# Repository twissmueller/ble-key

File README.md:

# ble-key

A Bluetooth Low Energy interface for a Morse **key**, built on a Seeed Studio XIAO board —
either the [XIAO ESP32-S3](https://wiki.seeedstudio.com/xiao_esp32s3_getting_started/) or the
[XIAO nRF52840](https://wiki.seeedstudio.com/XIAO_BLE/).

Plug in your own straight key or iambic paddle. The board reads the contacts (dit / dah),
debounces them, and streams **timed keying edges** over BLE as notifications to the
[Longpath](https://wissmueller.net/en/longpath.html) Morse-training app, which produces the
audio/sidetone and does the training. The device itself makes no sound — it's purely the
key interface. The onboard LED gives instant, BLE-independent visual feedback while keying.

The BLE contract below is simple and app-agnostic — anything that speaks GATT can consume it.
Both boards implement it identically; the app cannot tell them apart.

## Setting up your key

Plug your key or paddle (for example a Xiegu VK-5) into the 3.5 mm jack: tip is dit, ring is
dah, sleeve is ground; a straight key uses tip and sleeve only. Power the key from USB-C, then
connect to it from the Longpath app — it shows up as `Paddle`. The LED lights while you key,
so you can check the paddle before Bluetooth is involved. If dit and dah come out swapped,
switch your paddle's reverse setting (or its cable), not the key. A battery key sleeps after
ten idle minutes off USB; the first press only wakes it.

## Repository layout

| Path | What |
|------|------|
| [`esp32s3/`](esp32s3/) | XIAO ESP32-S3: firmware, pins and wiring, the battery mod ([BATTERY.md](esp32s3/BATTERY.md)) |
| [`nrf52840/`](nrf52840/) | XIAO nRF52840: firmware, pins and wiring, battery |
| [`lib/BleKeyCore/`](lib/BleKeyCore/src/BleKeyCore.h) | Shared firmware: the BLE contract, debounce, LiPo curve, power states |
| [`enclosure/`](enclosure/) | Printable cases — the XIAO case fits both boards |
| `flash.sh`, `monitor.sh` | Build, flash and watch either board |

## Which board?

| | XIAO ESP32-S3 | XIAO nRF52840 |
|---|---|---|
| Keying, LED, BLE contract | ✓ | ✓ |
| Wiring of the paddle jack | `D1` tip, `D2` ring, `GND` sleeve | the same |
| Battery level | LiPo **plus two dividers** soldered on | LiPo only — divider is on the board |
| Charging / charged | extra charge-sense wire | read from the charger on the board |
| Idle sleep | deep sleep, ~14 µA | System OFF, a few µA |
| Current while connected | tens of mA | a few mA (typical figures, not measured here) |

For a battery key the nRF52840 is the better choice: no extra parts and much longer runtime.
The ESP32-S3 key stays supported.

## Getting a key

The BLE key is open hardware — get one in whichever way suits you:

1. **Buy a ready-built key** in the [Ramus Labs Shop](https://shop.ramuslabs.com/ble-key/):
   assembled, flashed, and tested, in three cases (Mini, Compact, Modular).
2. **Build it yourself** — source the parts ([Hardware](#hardware)) and flash the firmware
   ([Build & flash](#build--flash)); everything you need is in this repository.

The Longpath app's BLE-key dialog offers only the shop (its address is set in Longpath's Darwin
config, `ble_key_shop_url`); building it yourself is documented here.

## BLE contract

The device advertises as **`Paddle`** with one service and one notify characteristic.
On every debounced paddle edge it sends a **5-byte little-endian** packet:

```
byte 0     : event   (uint8)
bytes 1..4 : millis  (uint32, little-endian) — device millis() at the edge
```

Events:

| Value | Event      |
|-------|------------|
| `0`   | `DIT_DOWN` |
| `1`   | `DIT_UP`   |
| `2`   | `DAH_DOWN` |
| `3`   | `DAH_UP`   |

The client reconstructs element and gap timing from consecutive timestamps. The board
re-advertises automatically after a central disconnects, so a client can reconnect
without power-cycling.

### Battery level

With a battery the key additionally exposes the SIG-standard
**Battery Service `0x180F`** with the **Battery Level characteristic `0x2A19`** (`uint8`,
0–100 %, read + notify). The level is re-measured every 10 s while the key is idle and
notified only when it changes; a client reads it once after connecting and then subscribes.
The service is *not* advertised — clients find it during service discovery — and it sits
next to the Longpath service without touching the packet format or UUIDs above. Clients
that do not know it, and older app builds, simply ignore it. Whether a key without a cell
exposes the service at all depends on the board (see its README); either way the Longpath
app then shows no level.

The percentage comes from an open-circuit LiPo discharge curve (3.30 V → 0 %, 4.20 V →
100 %, flat in the middle), not a linear map. On USB power the
measurement would only see the charger, so the key publishes **`0xFF` = level unknown** instead
of a percentage — outside the SIG's 0–100 on purpose; Longpath shows no level for it, other
clients should treat it the same way — and the idle sleep is off. Below 3.5 V the onboard
LED double-blinks once at boot, independently of BLE.

### Battery power state

Next to the level the same service carries the SIG-standard **Battery Power State
characteristic `0x2A1A`** (`uint8`, read + notify): bits 0–1 *present*, bits 2–3
*discharging*, bits 4–5 *charging* (each 2 = no, 3 = yes; 0 = unknown), bits 6–7 unused.
The key publishes five values:

| Meaning   | Value  | present | discharging | charging |
|-----------|--------|---------|-------------|----------|
| unknown   | `0x00` | ?       | ?           | ?        |
| on cell   | `0x2F` | yes     | yes         | no       |
| charging  | `0x3B` | yes     | no          | yes      |
| charged   | `0x2B` | yes     | no          | no       |
| no cell   | `0x02` | no      | —           | —        |

Off USB a plausible cell reading means *on cell*. On USB the charger's status line is the
only evidence; how each board reads it is in its README. Anything the key cannot vouch for
stays *unknown*. While *charging* or *charged* the level in `0x2A19`
is the live reading of the cell under charge instead of `0xFF` — a few points high and
climbing; the Longpath app shows it next to "charging" and forces 100 % once the key reports
*charged*. In every other state on USB the level stays `0xFF`. Notified only on change; a
client reads it once after connecting and subscribes.

### Idle sleep

A battery key enters deep sleep after ten minutes without a paddle edge.
It disconnects the central first, so a client sees a clean disconnect rather than a
supervision timeout, and wakes on either paddle line going LOW. Waking is a reset: the key
advertises again after about half a second, and `millis()` restarts at 0 — clients must
treat a reconnect as a timing resync (Longpath does). A key on USB never sleeps.

### UUIDs

The service and characteristic UUIDs in [`BleKeyCore.h`](lib/BleKeyCore/src/BleKeyCore.h) are the **fixed Longpath contract**
— the app looks for exactly this service, so leave them unchanged if your key should work
with Longpath (whether self-built, from a kit, or bought ready-made). Only when building
for a *different* client should you mint your own pair (`uuidgen`, run twice) and replace
`SVC_UUID` / `CHR_UUID` there — both boards pick them up.

## Build & flash

Requires [`arduino-cli`](https://arduino.github.io/arduino-cli/) and the core for your board:

```sh
# XIAO ESP32-S3
arduino-cli core install esp32:esp32
arduino-cli lib install "NimBLE-Arduino"

# XIAO nRF52840 (Seeed's non-mbed core, which brings the Bluefruit BLE library)
arduino-cli config add board_manager.additional_urls \
  https://files.seeedstudio.com/arduino/package_seeeduino_boards_index.json
arduino-cli core update-index
arduino-cli core install Seeeduino:nrf52
```

Then:

```sh
./flash.sh esp32s3            # or: ./flash.sh nrf52840
./flash.sh nrf52840 /dev/cu.usbmodemXXXX   # pass the port explicitly

./monitor.sh                  # serial monitor at 115200 baud, either board
```

`flash.sh` passes the shared `lib/BleKeyCore` to arduino-cli with `--library`; a manual
`arduino-cli compile` needs the same flag. Bench builds and board-specific notes are in
[esp32s3/README.md](esp32s3/README.md) and [nrf52840/README.md](nrf52840/README.md).

## License

[MIT](LICENSE) © 2026 Tobias Wissmüller

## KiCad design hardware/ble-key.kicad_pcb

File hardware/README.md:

# ble-key nRF52840 board — schematic

The custom board from [PCB-PLAN.md](../PCB-PLAN.md): a Raytac MDBT50Q-1MV2 (nRF52840), a BQ24074
charger with power path, USB-C, a 3.5 mm paddle jack and a JST-PH socket for the LiPo.

| File | What |
|---|---|
| `ble-key.kicad_pro`, `ble-key.kicad_sch` | KiCad 10 project and schematic — open the project in KiCad |
| `ble-key-schematic.pdf` | the schematic as a PDF |
| `ble-key-bom.csv` | parts list with MPNs where chosen |
| `gen_schematic.py` | generates the schematic; the parts, values and nets live here |
| `ble-key.kicad_pcb` | the board: 48 × 27 mm, 2 layers, routed |
| `gen_board.py` | places the footprints, draws outline, holes, pours and the antenna keep-out |
| `route.py` | autoroutes the board with Freerouting, stitches the ground pours and refills them |
| `board-top.png`, `board-bottom.png` | renders of the routed board |
| `export_jlc.py`, `jlcpcb/` | JLCPCB production files: Gerbers + drill (zip), BOM and placement (CPL) |

**Status:** schematic and a first routed layout. ERC: 0 errors. DRC: 0 errors and 0 unconnected
pads; the remaining warnings are the paddle jack's outline crossing the board edge (its opening
overhangs the edge on purpose) and, until KiCad has been opened once, "library not in the
configuration" notices.

## Design

| Block | Choice |
|---|---|
| USB-C | GCT USB4105, 5.1 kΩ on CC1/CC2 (5 V sink), USBLC6-2SC6 ESD, 27 Ω series resistors to the module (Raytac reference) |
| Charger | BQ24074: 175 mA charge (R_ISET 5.1 kΩ, 0.5 C for 350 mAh), 500 mA input limit (R_ILIM 3.09 kΩ, EN2 = 1, EN1 = 0), TS on 10 kΩ (no thermistor), ITERM and TMR open for the datasheet defaults (10 % termination, 5 h safety timer) |
| Power | BQ24074 OUT (VSYS: 4.4 V on USB, battery voltage otherwise) feeds the module's VDDH. VDD is the module's own 3.3 V output, through its REG0 DC/DC converter with L1 (Raytac spec §8.1) |
| Module | MDBT50Q-1MV2, 32.768 kHz crystal on P0.00/P0.01 (the module has none) |
| Battery level | 1 MΩ + 1 MΩ divider with 100 nF into P0.29 / AIN5, about 2 µA drain |
| Charger status | ~PGOOD (USB present) on P0.30, ~CHG (charging) on P0.31, 100 kΩ pull-ups to VDD |
| Paddle | tip → 470 Ω → P0.04 (dit), ring → 470 Ω → P0.06 (dah), sleeve → GND; internal pull-ups |
| LEDs, reset | red P1.15, blue P1.10 — the Feather nRF52840 pins, so its bootloader drives them; reset button on P0.18 |
| Programming | Tag-Connect TC2030 pads for SWD (no part fitted) |

## Layout

- **48 × 27 mm, 2 layers, 1.6 mm, ENIG** (AISLER 2-layer ENIG rules: 0.125 mm track and space).
  Ground pour on both sides.
- **Module** at the top edge, antenna outward, with a copper-free strip along the top edge
  (12–35 mm, 4.2 mm deep) on both layers, wider than Raytac's minimum.
- **USB-C** on the right edge, **paddle jack** on the left edge, **battery JST** at the top-left
  with its plug pointing inward (the cell sits above the board in the case lid), **status LEDs** in
  the top-right corner, **reset button** on the bottom edge (side push).
- **SWD pads** (Tag-Connect TC2030-NL) on the back, bottom-left. Two M2 mounting holes.
- Net classes: signals 0.2 mm, power 0.3 mm, the reset line 0.15 mm so it can escape from the
  module's inner pad row.

**Ground:** routed like every other net first, so each pad has a real connection. Then about 145
stitching vias (0.6 mm, on a 1 mm grid wherever both pours have room) tie the front and back pours
together, a few 0.45 mm vias join pour patches that traces cut off, and the charger's exposed pad
has four thermal vias. KiCad's connectivity check finds no unconnected copper.

**Still worth a human look before ordering:** the USB pair is routed as two single tracks (fine
for 12 Mbit/s full speed), and the enclosure in `../enclosure/` is drawn around this board.
Raytac offers a free layout review.

## Open points

- **UICR.REGOUT0 = 3.3 V** must be written when the bootloader is flashed over SWD. In VDDH mode
  the nRF52840 starts with VDD at 1.8 V.
- **BQ24074 footprint:** KiCad's default has a 1.6 mm exposed pad, TI's drawing for the related
  RGT0016C package shows 1.68 mm. Check TI's RGT0016B drawing for the BQ24074 and pick the matching
  footprint.
- **Reset switch:** the footprint is Panasonic EVQ-PUC (side push). The EVP-AKE31A from the plan
  has no footprint in KiCad's library and would need a custom one.
- **MPNs still to choose** for the passives, L1 (10 µH 0603, ≥ 80 mA) and Y1 (32.768 kHz,
  2.0 × 1.2 mm, load capacitance matching the 12 pF capacitors), so AISLER can match them.
- **Layout rules from Raytac:** module at the board edge with the antenna end outward, a 3.8 mm
  copper-free strip across the antenna end on every layer, plenty of GND vias at the module corners.
  Raytac reviews layouts for free (service@raytac.com).

## JLCPCB

`python3 export_jlc.py` writes `jlcpcb/ble-key-gerbers.zip`, `jlcpcb/ble-key-bom.csv` and
`jlcpcb/ble-key-cpl.csv` for JLCPCB's PCB + SMT assembly order. The parts come from the schematic's
`LCSC` fields (the table at the top of `gen_schematic.py`). Choose 2 layers, 1.6 mm, ENIG, and
assembly on the top side only.

As of 1 October 2026:

- **Out of stock:** the MDBT50Q-1MV2 module (C5118826, 0 at JLCPCB and LCSC) and the EVQ-PUC02K
  reset switch (C79174, 1 left). Pre-order them into the JLCPCB parts library, or send them in.
- **Extended parts** (each adds JLCPCB's setup fee): the module, charger, ESD chip, USB-C, jack,
  JST, switch, inductor, crystal, blue LED, 3.09 kΩ and 27 Ω. The rest are Basic parts.
- **Different makers than the AISLER build** for the generic parts (red/blue LED, 12 pF), same
  values and packages.
- **Rotations:** after uploading, check JLCPCB's placement preview; parts their library orients
  differently get a correction in `ROTATION_FIX` in `export_jlc.py`.

## Regenerating

Schematic, then board, then routing:

```bash
.venv/bin/python gen_schematic.py
/Applications/KiCad/KiCad.app/Contents/MacOS/kicad-cli sch export netlist -o ble-key.net ble-key.kicad_sch
/Applications/KiCad/KiCad.app/Contents/Frameworks/Python.framework/Versions/Current/bin/python3 gen_board.py
/Applications/KiCad/KiCad.app/Contents/Frameworks/Python.framework/Versions/Current/bin/python3 route.py 100
/Applications/KiCad/KiCad.app/Contents/MacOS/kicad-cli pcb drc ble-key.kicad_pcb
```

`route.py` runs Freerouting 2.4.1 in its Docker image (`ghcr.io/freerouting/freerouting:2.4.1`,
no network access). Each run may route slightly differently.

### Schematic symbols

The generator copies symbols from KiCad's standard libraries into `.kilib/` (not committed):

```bash
uv venv --python 3.12 .venv && uv pip install --python .venv/bin/python -r requirements.txt
mkdir -p .kilib && docker run --rm --platform linux/amd64 -v "$PWD/.kilib":/out kicad/kicad:10.0 bash -c 'cd /usr/share/kicad/symbols && cp RF_Module.kicad_sym Battery_Management.kicad_sym Connector.kicad_sym Connector_Audio.kicad_sym Power_Protection.kicad_sym Device.kicad_sym Switch.kicad_sym power.kicad_sym /out/'
.venv/bin/python gen_schematic.py
```

With KiCad installed, the libraries can be copied from `/Applications/KiCad/KiCad.app/Contents/SharedSupport/symbols/`
instead, and `kicad-cli sch erc ble-key.kicad_sch` checks the result.

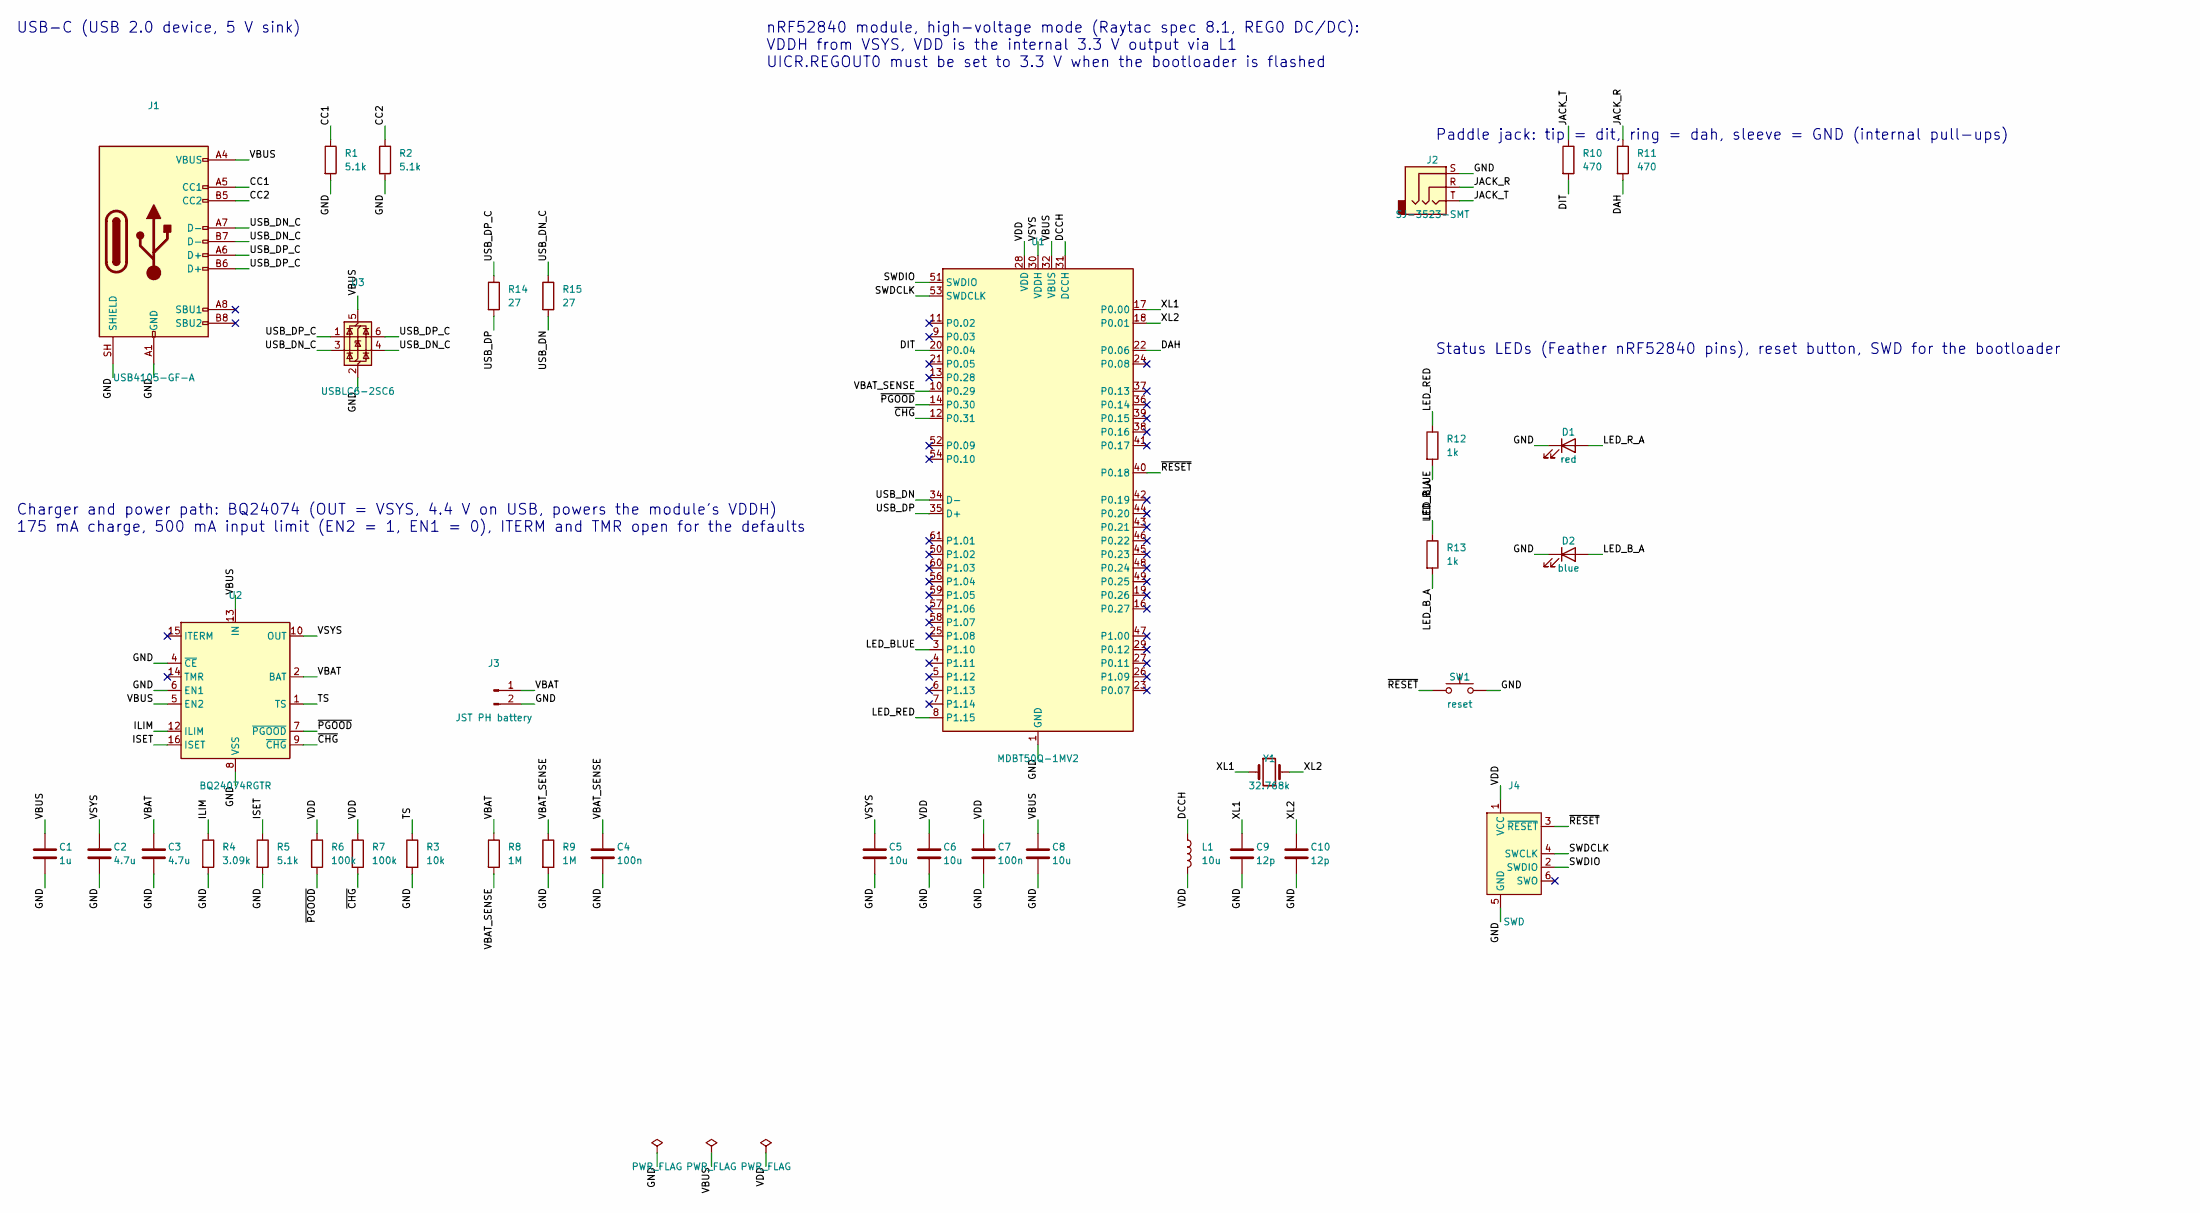
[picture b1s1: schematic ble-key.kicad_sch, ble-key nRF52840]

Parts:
C1: 1u; C_0402_1005Metric
C2, C3: 4.7u; C_0603_1608Metric
C4, C7: 100n; C_0402_1005Metric
C5, C6, C8: 10u; C_0603_1608Metric
C9, C10: 12p; C_0402_1005Metric
D1: red; LED_0603_1608Metric; MPN 150060RS75000
D2: blue; LED_0603_1608Metric; MPN 150060BS75000
J1: USB4105-GF-A; USB_C_Receptacle_GCT_USB4105-xx-A_16P_TopMnt_Horizontal; MPN USB4105-GF-A
J2: SJ-3523-SMT; Jack_3.5mm_CUI_SJ-3523-SMT_Horizontal; MPN SJ-3523-SMT-TR
J3: JST PH battery; JST_PH_S2B-PH-SM4-TB_1x02-1MP_P2.00mm_Horizontal; MPN S2B-PH-SM4-TB(LF)(SN)
J4: SWD; Tag-Connect_TC2030-IDC-NL_2x03_P1.27mm_Vertical
L1: 10u; L_0603_1608Metric
R1, R2, R5: 5.1k; R_0402_1005Metric
R3: 10k; R_0402_1005Metric
R4: 3.09k; R_0402_1005Metric
R6, R7: 100k; R_0402_1005Metric
R8, R9: 1M; R_0402_1005Metric
R10, R11: 470; R_0402_1005Metric
R12, R13: 1k; R_0402_1005Metric
R14, R15: 27; R_0402_1005Metric
SW1: reset; Panasonic_EVQPUL_EVQPUC; MPN EVQ-PUC02K
U1: MDBT50Q-1MV2; Raytac_MDBT50Q; MPN MDBT50Q-1MV2
U2: BQ24074RGTR; VQFN-16-1EP_3x3mm_P0.5mm_EP1.6x1.6mm; MPN BQ24074RGTR
U3: USBLC6-2SC6; SOT-23-6; MPN USBLC6-2SC6
Y1: 32.768k; Crystal_SMD_2012-2Pin_2.0x1.2mm

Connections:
CC1: J1.A5 (CC1), R1.1
CC2: J1.B5 (CC2), R2.1
DAH: R11.2, U1.22 (P0.06)
DCCH: L1.1, U1.31 (DCCH)
DIT: R10.2, U1.20 (P0.04)
GND: C1.2, C2.2, C3.2, C4.2, C5.2, C6.2, C7.2, C8.2, C9.2, C10.2, D1.1 (K), D2.1 (K), J1.A1 (GND), J1.A12 (GND), J1.B1 (GND), J1.B12 (GND), J1.SH (SHIELD), J2.S, J3.2, J4.5 (GND), R1.2, R2.2, R3.2, R4.2, R5.2, R9.2, SW1.2, U1.1 (GND), U1.2 (GND), U1.15 (GND), U1.33 (GND), U1.55 (GND), U2.4 (~CE), U2.6 (EN1), U2.8 (VSS), U2.17 (VSS), U3.2 (GND)
ILIM: R4.1, U2.12 (ILIM)
ISET: R5.1, U2.16 (ISET)
JACK_R: J2.R, R11.1
JACK_T: J2.T, R10.1
LED_BLUE: R13.1, U1.3 (P1.10)
LED_B_A: D2.2 (A), R13.2
LED_RED: R12.1, U1.8 (P1.15)
LED_R_A: D1.2 (A), R12.2
SWDCLK: J4.4 (SWCLK), U1.53 (SWDCLK)
SWDIO: J4.2 (SWDIO), U1.51 (SWDIO)
TS: R3.1, U2.1 (TS)
USB_DN: R15.2, U1.34 (D-)
USB_DN_C: J1.A7 (D-), J1.B7 (D-), R15.1, U3.3 (I/O2), U3.4 (I/O2)
USB_DP: R14.2, U1.35 (D+)
USB_DP_C: J1.A6 (D+), J1.B6 (D+), R14.1, U3.1 (I/O1), U3.6 (I/O1)
VBAT: C3.1, J3.1, R8.1, U2.2 (BAT), U2.3 (BAT)
VBAT_SENSE: C4.1, R8.2, R9.1, U1.10 (P0.29)
VBUS: C1.1, C8.1, J1.A4 (VBUS), J1.A9 (VBUS), J1.B4 (VBUS), J1.B9 (VBUS), U1.32 (VBUS), U2.5 (EN2), U2.13 (IN), U3.5 (VBUS)
VDD: C6.1, C7.1, J4.1 (VCC), L1.2, R6.1, R7.1, U1.28 (VDD)
VSYS: C2.1, C5.1, U1.30 (VDDH), U2.10 (OUT), U2.11 (OUT)
XL1: C9.1, U1.17 (P0.00), Y1.1
XL2: C10.1, U1.18 (P0.01), Y1.2
~CHG: R7.2, U1.12 (P0.31), U2.9 (~CHG)
~PGOOD: R6.2, U1.14 (P0.30), U2.7 (~PGOOD)
~RESET: J4.3 (~RESET), SW1.1, U1.40 (P0.18)

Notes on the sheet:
USB-C (USB 2.0 device, 5 V sink)
Charger and power path: BQ24074 (OUT = VSYS, 4.4 V on USB, powers the module's VDDH) 175 mA charge, 500 mA input limit (EN2 = 1, EN1 = 0), ITERM and TMR open for the defaults
nRF52840 module, high-voltage mode (Raytac spec 8.1, REG0 DC/DC): VDDH from VSYS, VDD is the internal 3.3 V output via L1 UICR.REGOUT0 must be set to 3.3 V when the bootloader is flashed
Paddle jack: tip = dit, ring = dah, sleeve = GND (internal pull-ups)
Status LEDs (Feather nRF52840 pins), reset button, SWD for the bootloader

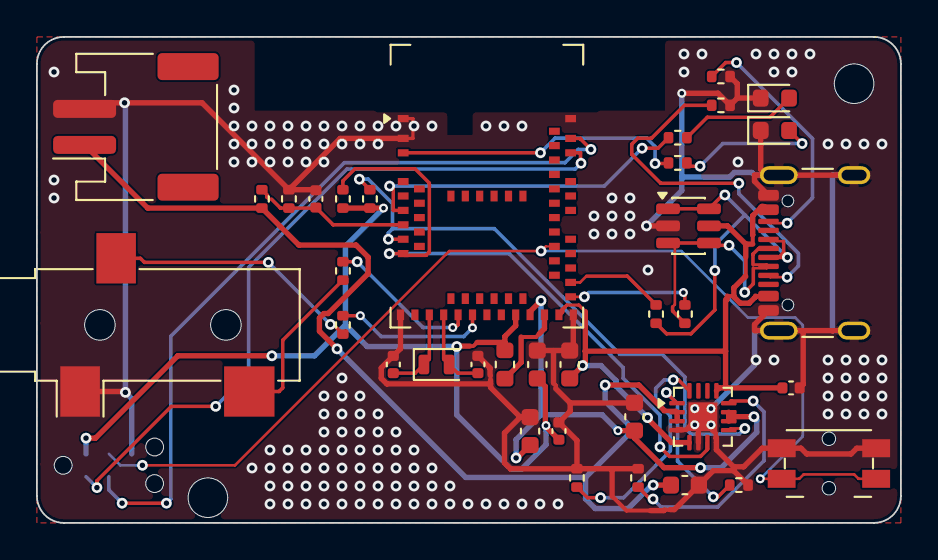
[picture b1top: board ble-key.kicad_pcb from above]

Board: 2 copper layers, 48.0 x 27.0 mm, 39 parts (1 on the bottom side), 31 nets.

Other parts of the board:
H1, H2: M2; MountingHole_2.2mm_M2

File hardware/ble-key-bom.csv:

"Reference","Value","Footprint","MPN","QUANTITY"
"C1","1u","Capacitor_SMD:C_0402_1005Metric","","1"
"C2,C3","4.7u","Capacitor_SMD:C_0603_1608Metric","","2"
"C4,C7","100n","Capacitor_SMD:C_0402_1005Metric","","2"
"C5,C6,C8","10u","Capacitor_SMD:C_0603_1608Metric","","3"
"C9,C10","12p","Capacitor_SMD:C_0402_1005Metric","","2"
"D1","red","LED_SMD:LED_0603_1608Metric","150060RS75000","1"
"D2","blue","LED_SMD:LED_0603_1608Metric","150060BS75000","1"
"J1","USB4105-GF-A","Connector_USB:USB_C_Receptacle_GCT_USB4105-xx-A_16P_TopMnt_Horizontal","USB4105-GF-A","1"
"J2","SJ-3523-SMT","Connector_Audio:Jack_3.5mm_CUI_SJ-3523-SMT_Horizontal","SJ-3523-SMT-TR","1"
"J3","JST PH battery","Connector_JST:JST_PH_S2B-PH-SM4-TB_1x02-1MP_P2.00mm_Horizontal","S2B-PH-SM4-TB(LF)(SN)","1"
"L1","10u","Inductor_SMD:L_0603_1608Metric","","1"
"R1,R2,R5","5.1k","Resistor_SMD:R_0402_1005Metric","","3"
"R3","10k","Resistor_SMD:R_0402_1005Metric","","1"
"R4","3.09k","Resistor_SMD:R_0402_1005Metric","","1"
"R6,R7","100k","Resistor_SMD:R_0402_1005Metric","","2"
"R8,R9","1M","Resistor_SMD:R_0402_1005Metric","","2"
"R10,R11","470","Resistor_SMD:R_0402_1005Metric","","2"
"R12,R13","1k","Resistor_SMD:R_0402_1005Metric","","2"
"R14,R15","27","Resistor_SMD:R_0402_1005Metric","","2"
"SW1","reset","Button_Switch_SMD:Panasonic_EVQPUL_EVQPUC","EVQ-PUC02K","1"
"U1","MDBT50Q-1MV2","RF_Module:Raytac_MDBT50Q","MDBT50Q-1MV2","1"
"U2","BQ24074RGTR","Package_DFN_QFN:VQFN-16-1EP_3x3mm_P0.5mm_EP1.6x1.6mm","BQ24074RGTR","1"
"U3","USBLC6-2SC6","Package_TO_SOT_SMD:SOT-23-6","USBLC6-2SC6","1"
"Y1","32.768k","Crystal:Crystal_SMD_2012-2Pin_2.0x1.2mm","","1"

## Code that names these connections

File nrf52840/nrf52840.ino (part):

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
// ---- Pins ----
// Same XIAO pads as on the ESP32-S3 key, so the wiring and the case are unchanged.
const int PIN_DIT      = D1;         // P0.03, Tip
const int PIN_DAH      = D2;         // P0.28, Ring
const int PIN_KEY_LED  = LED_BLUE;   // P0.06, keying feedback
const int PIN_WARN_LED = LED_RED;    // P0.26, low-battery blink at boot
const int PIN_CHG      = 23;         // P0.17, BQ25100 ~CHG, LOW = charging (no name in the variant)
// PIN_VBAT (P0.31) and VBAT_ENABLE (P0.14) come from the variant.
// The RGB LED is active-low (LOW = on), whatever LED_STATE_ON in the variant says.

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  // what wakes the chip.
  digitalWrite(PIN_KEY_LED, HIGH);
  digitalWrite(PIN_WARN_LED, HIGH);
  nrf_gpio_cfg_sense_input(g_ADigitalPinMap[PIN_DIT], NRF_GPIO_PIN_PULLUP, NRF_GPIO_PIN_SENSE_LOW);
  nrf_gpio_cfg_sense_input(g_ADigitalPinMap[PIN_DAH], NRF_GPIO_PIN_PULLUP, NRF_GPIO_PIN_SENSE_LOW);
  delay(5);

  uint8_t sdEnabled = 0;
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  uint32_t latch = NRF_P0->LATCH;
  NRF_P0->LATCH = latch;                           // write-1-to-clear
  wokeFromSleep = readResetReason() & POWER_RESETREAS_OFF_Msk;
  wokeOnDah = latch & (1UL << g_ADigitalPinMap[PIN_DAH]);

  Serial.begin(115200);
  // Woken by a key press? Then every millisecond counts towards the reconnect — skip the
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  if (wokeFromSleep) logf("\n[paddle] woke on key press (%s)\n", wokeOnDah ? "dah" : "dit");
  else               logf("\n[paddle] boot (reset reason 0x%08lx)\n", readResetReason());

  pinMode(PIN_DIT, INPUT_PULLUP);                  // also clears the SENSE setting of the sleep
  pinMode(PIN_DAH, INPUT_PULLUP);
  pinMode(PIN_KEY_LED, OUTPUT);
  digitalWrite(PIN_KEY_LED, HIGH);                     // off (active-low)
  pinMode(PIN_WARN_LED, OUTPUT);
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  // divider and keeps the pin safe, in System OFF as well.
  pinMode(VBAT_ENABLE, OUTPUT);
  digitalWrite(VBAT_ENABLE, LOW);
  pinMode(PIN_CHG, INPUT_PULLUP);
  analogReference(AR_INTERNAL_2_4);
  analogReadResolution(12);
  analogSampleTime(40);
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    logConnParams("settled");
  }

  bool ditSample = (digitalRead(PIN_DIT) == LOW);  // pressed = LOW
  bool dahSample = (digitalRead(PIN_DAH) == LOW);

  if (dit.update(ditSample, now)) {
    sendEvent(dit.reported ? DIT_DOWN : DIT_UP);
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
  // ~CHG is cheap to sample, so it is watched on every pass; its verdict, once a window, is
  // what moves the power state while on USB.
  bool ledJudged = chargeLed.sample(digitalRead(PIN_CHG) == LOW, now);
  if (onUsb && (ledJudged || usbJustArrived)) {
    publishPowerState(judgePowerState(true, usbJustArrived, ledJudged, chargeLed.verdict));
  }
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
